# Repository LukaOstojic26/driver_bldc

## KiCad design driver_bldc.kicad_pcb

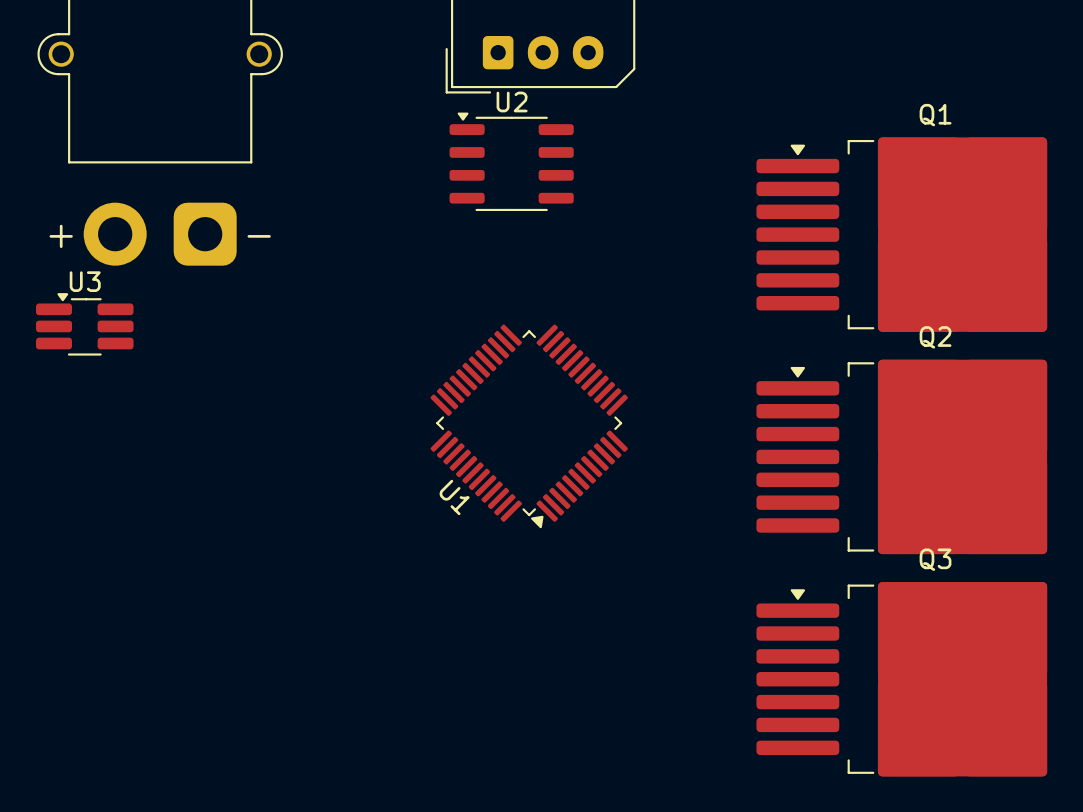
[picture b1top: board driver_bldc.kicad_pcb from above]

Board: 2 copper layers, 8 parts (0 on the bottom side), 10 nets, no tracks yet.

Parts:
J1: CAN; Molex_SPOX_5267-03A_1x03_P2.50mm_Vertical
J3: BATT; AMASS_XT30PW-M_1x02_P2.50mm_Horizontal
Q1, Q2, Q3: BTN8982TA; TO-263-7_TabPin8
U1: STM32G431CBT6; LQFP-48_7x7mm_P0.5mm
U2: SN65HVD234; SOIC-8_3.9x4.9mm_P1.27mm
U3: AP63203WU; TSOT-23-6_HandSoldering

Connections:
+3.3V: U1.1 (VBAT), U1.24 (VDD), U1.36 (VDD), U1.48 (VDD), U2.3 (VCC), U3.1 (FB)
+24V: J3.1, U3.2 (EN), U3.3 (IN)
/CANH: J1.2, U2.7 (CANH)
/CANL: J1.3, U2.6 (CANL)
A: Q1.4, Q1.8
B: Q2.4, Q2.8
C: Q3.4, Q3.8
CAN_RX+: U1.33 (PA11), U2.4 (R)
CAN_TX-: U1.34 (PA12), U2.1 (D)
GND: J1.1, J3.2, U1.19 (VSSA), U1.23 (VSS), U1.35 (VSS), U1.47 (VSS), U2.2 (GND), U2.8 (Rs), U3.4 (GND)

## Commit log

2025-07-10 prvi commit
2025-07-13 dodati decoupling C i NRST
2025-07-15 CAN dodat
2025-07-17 dodat buck
2025-07-17 buck dodat
